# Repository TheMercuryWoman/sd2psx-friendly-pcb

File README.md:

as of right now its based on rp2040 zero waveshare, all credits goes to moahdib from bitbuild and the sd2psx team. I will plan on to make a pcb based on for rp2040 waveshare and the normal pico. Also the psram will be used in here will be for adafruit 4766 since I couldnt find the other recommended ones and there were some confirmation that it works with sd2psx

The hardware is based on :

- RP2040 Zero board
- PSRAM 8MB 8pin SOIC
- 0.96 inch OLED 128x64 SSD1306 (dual color with yellow and blue works great)
- 2 buttons for left and right
- 3.3V Micro SD card reader as pictured

- Should have full functionality as commercially available sd2psx memcards.

Sidenot: Do not order any pcbs unless I made the gerbers avaliable, it still at prototype stage and I have to check if the 4677 adafruit psrams works

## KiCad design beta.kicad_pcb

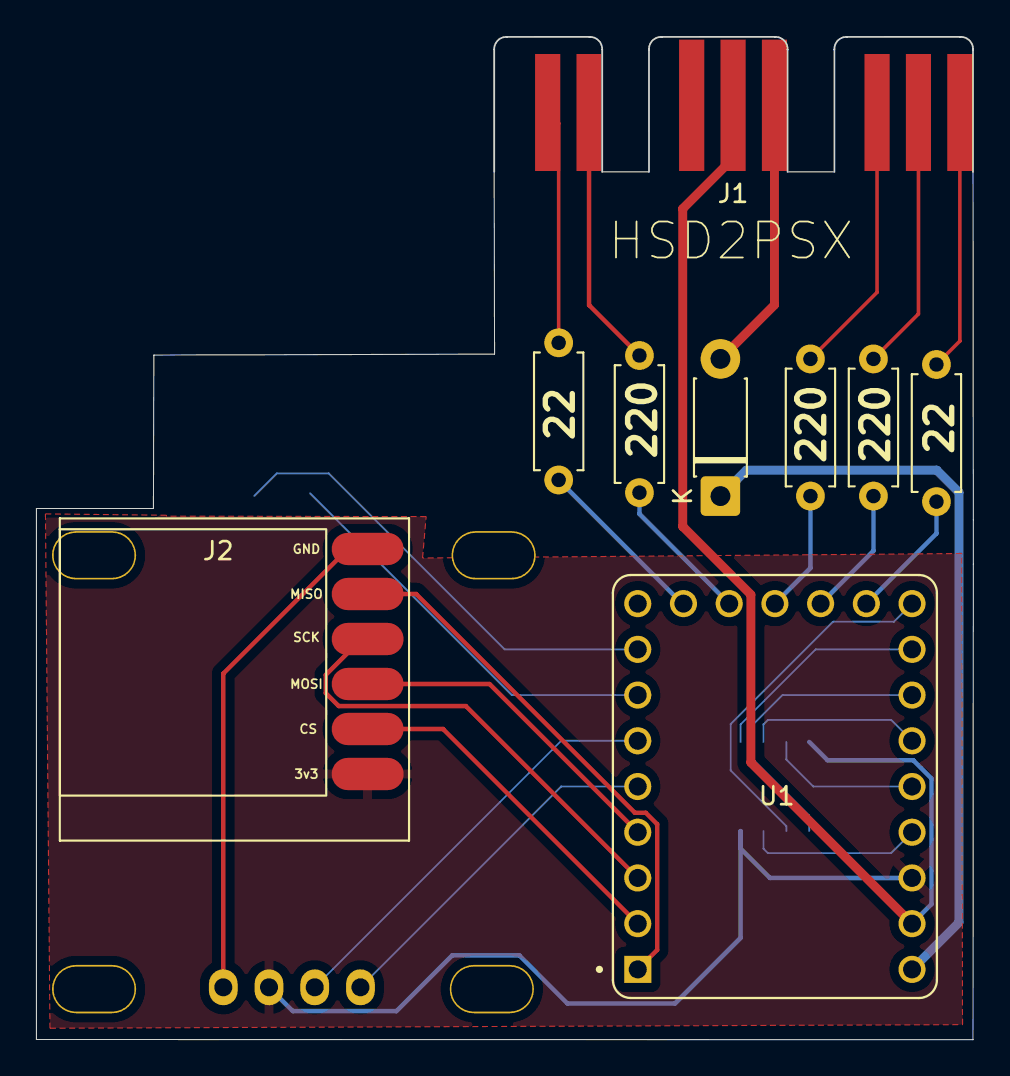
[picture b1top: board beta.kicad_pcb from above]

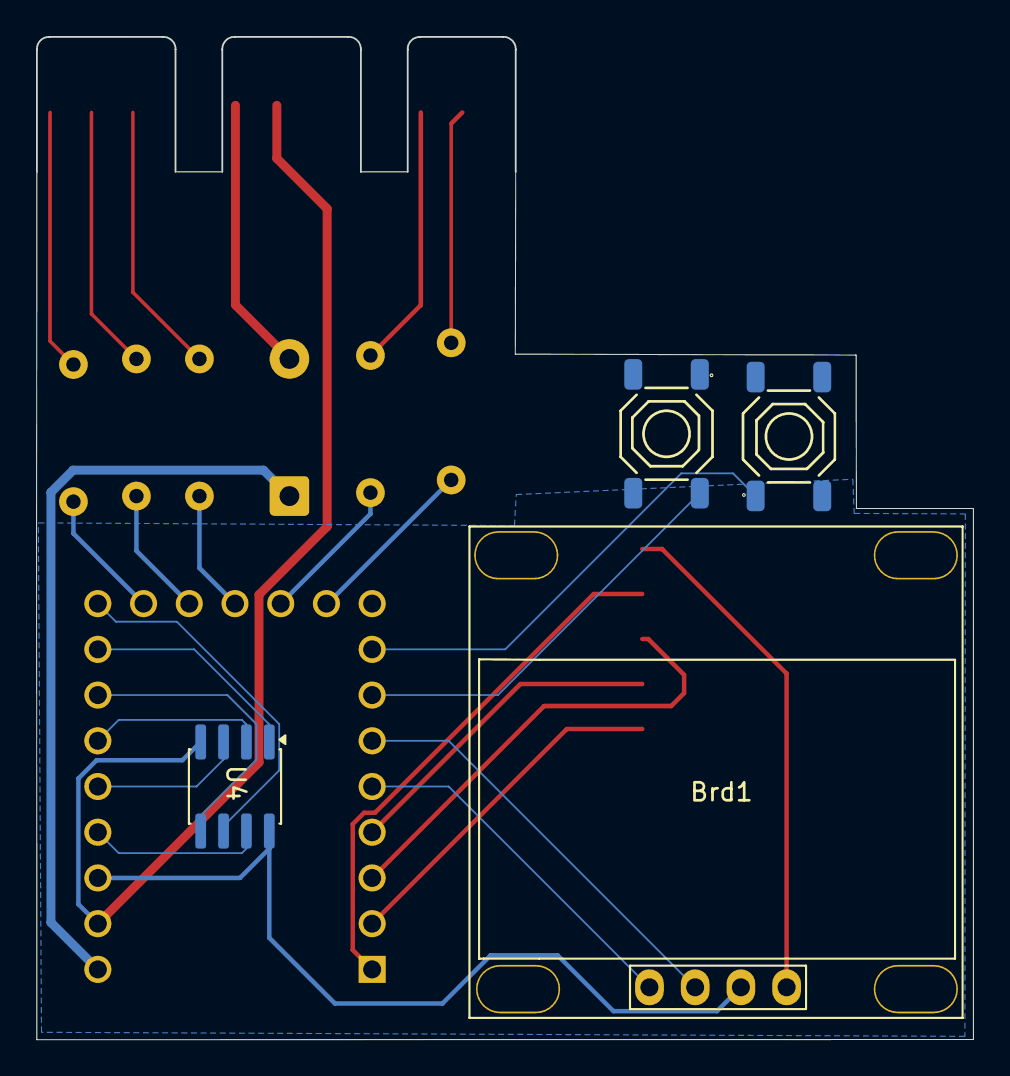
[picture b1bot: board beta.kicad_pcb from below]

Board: 2 copper layers, 52.0 x 55.7 mm, 13 parts (4 on the bottom side), 28 nets.

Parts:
Brd1: SSD1306; 128x64OLED
D1: D_Schottky; D_DO-41_SOD81_P7.62mm_Horizontal
J1: PSX Memory Card Interface; MemoryCardConnector
J2: MicroSD SPI; MicroSD_SPI_small
R10, R14: 22; R_Axial_DIN0207_L6.3mm_D2.5mm_P7.62mm_Horizontal
R11, R12, R13: 220; R_Axial_DIN0207_L6.3mm_D2.5mm_P7.62mm_Horizontal
S1, S2: Tactile Button, 160gf; SW-SMD_4P-L5.1-W5.1-P3.70-LS6.5-TL-2
U1: RP2040-ZERO; MODULE_RP2040-ZERO
U4: psram; SOIC-8_3.9x4.9mm_P1.27mm

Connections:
+3V3: Brd1.2 (VCC), J2.1, U1.21 (3V3), U4.8 (VCC)
GND: Brd1.1 (GND), J1.4 (GND), J2.6, S1.3 (C), S2.4 (D), U1.22 (GND), U4.4 (VSS)
MISO: J2.5, U1.1 (GP0)
MOSI: J2.3, U1.4 (GP3)
unnamed: D1.1 (K), U1.23 (5V)
unnamed: R14.2, U1.10 (GP9)
unnamed: R13.2, U1.11 (GP10)
unnamed: R11.2, U1.12 (GP11)
unnamed: R12.2, U1.13 (GP12)
unnamed: R10.2, U1.14 (GP13)
OLED_SCL: Brd1.3 (SCL), U1.6 (GP5)
OLED_SDA: Brd1.4 (SDA), U1.5 (GP4)
PSRAM_CLK: U1.15 (GP14), U4.6 (SCLK)
PSRAM_CS: U1.16 (GP15), U4.1 (~CE)
PSRAM_IO0: U1.17 (GP26), U4.5 (SI/SIO)
PSRAM_IO1: U1.18 (GP27), U4.2 (SO/SIO)
PSRAM_IO2: U1.19 (GP28), U4.3 (SIO2)
PSRAM_IO3: U1.20 (GP29), U4.7 (SIO3)
PSX_3.5V: D1.2 (A), J1.5 (5V)
PSX_ACK: J1.8 (ACK), R10.1
PSX_CLK: J1.7 (CLK), R12.1
PSX_CMD: J1.2 (CMD), R13.1
PSX_DAT: J1.1 (DAT), R14.1
PSX_SEL: J1.6 (SEL), R11.1
SCK: J2.4, U1.3 (GP2)
SS: J2.2, U1.2 (GP1)
SW2: S1.1 (A), U1.8 (GP7)
SW3: S2.2 (B), U1.7 (GP6)

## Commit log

2026-03-03 Add initial README content with credits
2026-03-03 Update README with project details and component info
    Expanded the description regarding the RP2040 project and components used.
2026-03-04 Add files via upload
    heres a idea of the pcb, i know it is terrible but im a beginner so any help is welcome
2026-03-05 Add files via upload
    changes the pcb to be more compacted, added the tactile buttons and made the layers gnd and 3.3v
2026-03-07 Update README with hardware details and credits
    Added hardware specifications and credits for the project.
2026-03-09 Add files via upload
    Here oled and buttons should be properly visible while plugged in, i am waiting for a part to test if 4677 works and if it does i will order the pcbs to see that would work, please PLEASE dont order 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
2026-03-09 Add files via upload
    thanks github for not updating anything
